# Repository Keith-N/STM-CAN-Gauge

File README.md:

# STM-CAN-Gauge

An STM32F042 based CAN gauge for use with rusEFI ECUs. <br/>
CAN is configured for 500k with a base ID of 512. <br/>
Input voltage tested at 5V and 12V. <br/>

Flash 'CAN Gauge.bin' through STM32CubeProgrammer using STLink and TC2030. <br/>

The only required connections for operation are supply voltage/ground and CAN High/Low. <br/>

Pinout from the back of connector.

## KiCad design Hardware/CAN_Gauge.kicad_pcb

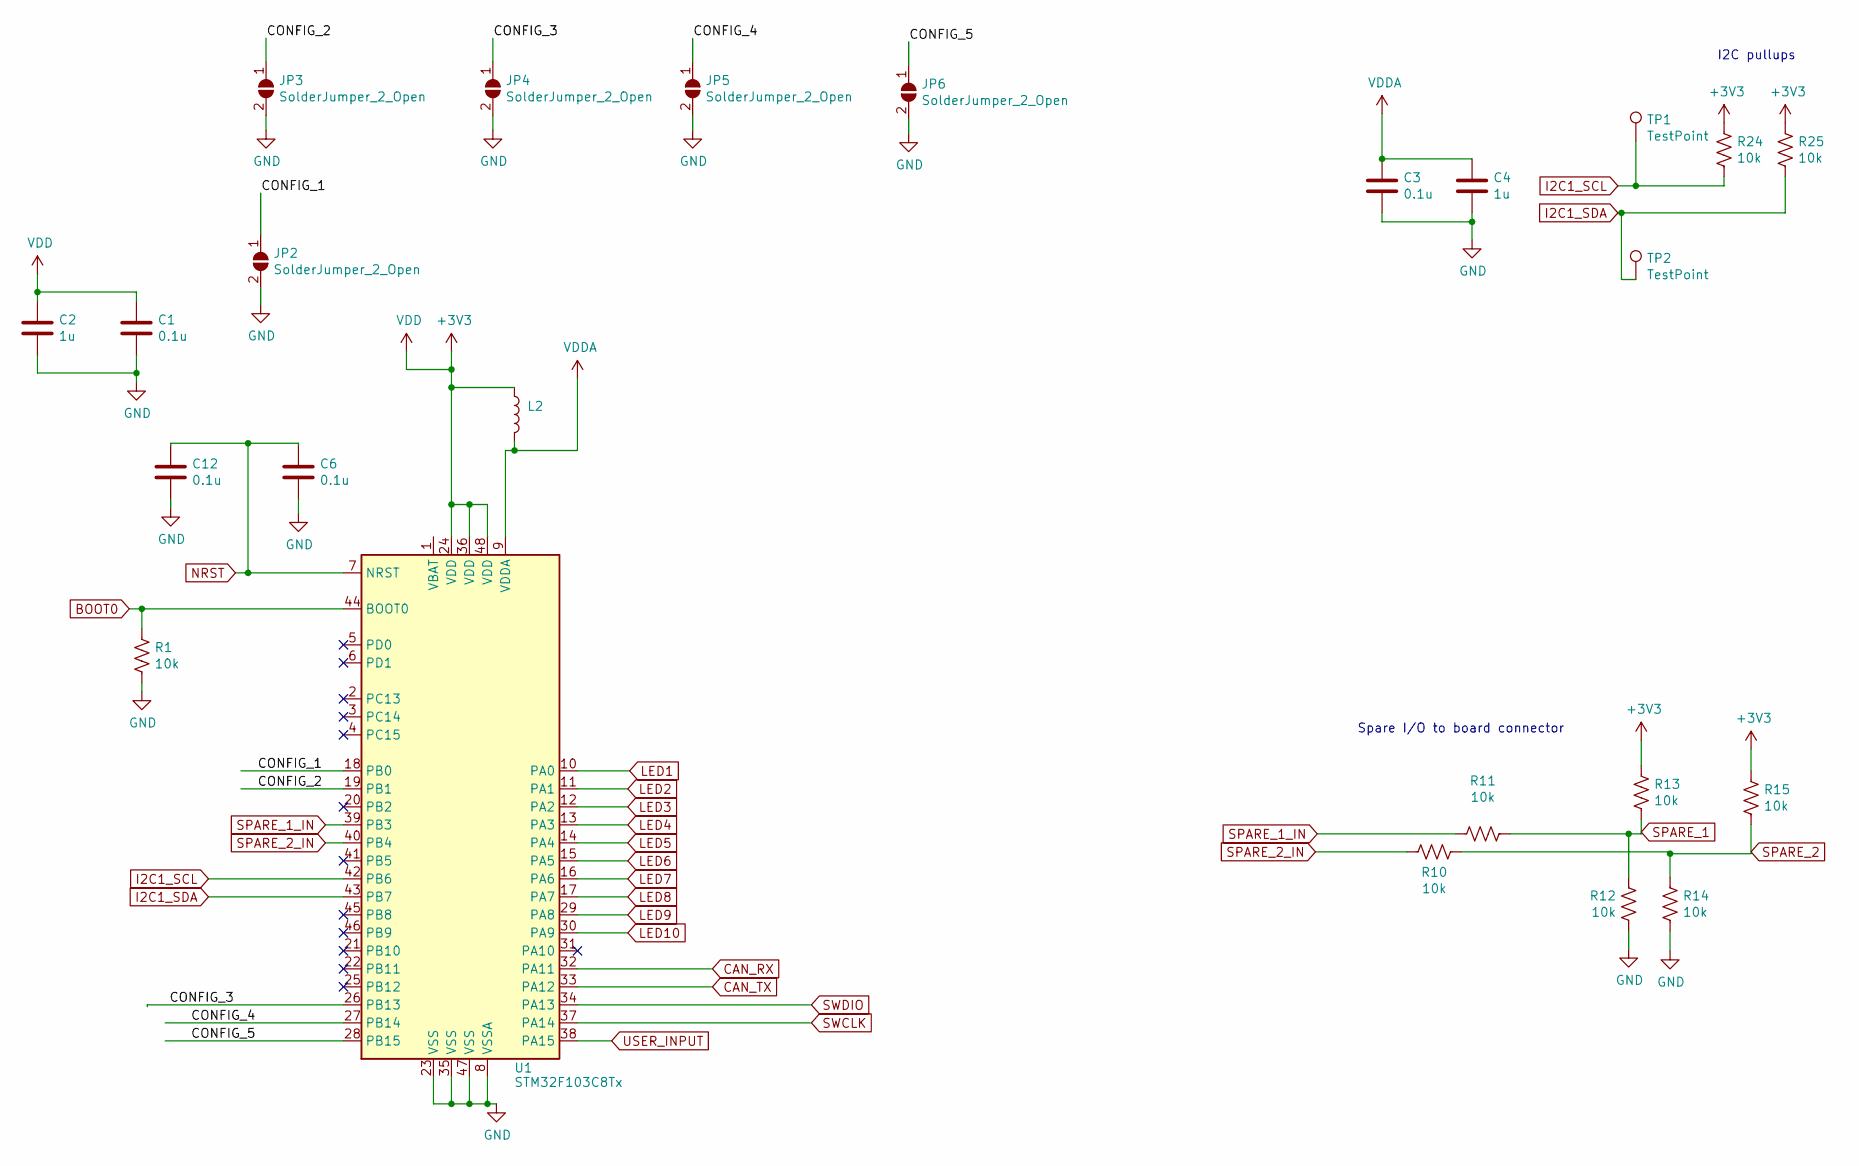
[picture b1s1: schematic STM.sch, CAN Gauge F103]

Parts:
C1, C3, C6, C12: 0.1u; C_0402_1005Metric; LCSC C2655418
C2, C4: 1u; C_0402_1005Metric; LCSC C389008
JP2, JP3, JP4, JP5, JP6: SolderJumper_2_Open; SolderJumper-2_P1.3mm_Open_Pad1.0x1.5mm
L2: 30; L_0402_1005Metric; LCSC C76886
R1, R10, R11, R12, R13, R14, R15, R24, R25: 10k; R_0402_1005Metric
TP1, TP2: TestPoint; TestPoint_Pad_D1.0mm
U1: STM32F103C8Tx; LQFP-48_7x7mm_P0.5mm; LCSC C8734

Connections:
/STM/CONFIG_1: JP2.1 (A), U1.18 (PB0)
/STM/CONFIG_2: JP3.1 (A), U1.19 (PB1)
/STM/CONFIG_3: JP4.1 (A), U1.26 (PB13)
/STM/CONFIG_4: JP5.1 (A), U1.27 (PB14)
/STM/CONFIG_5: JP6.1 (A), U1.28 (PB15)
BOOT0: R1.1, U1.44 (BOOT0)
CAN_RX: U1.32 (PA11); also elsewhere on the board
CAN_TX: U1.33 (PA12); also elsewhere on the board
GND: C1.2, C2.2, C3.2, C4.2, C6.2, C12.2, JP2.2 (B), JP3.2 (B), JP4.2 (B), JP5.2 (B), JP6.2 (B), R1.2, R12.1, R14.1, U1.8 (VSSA), U1.23 (VSS), U1.35 (VSS), U1.47 (VSS); also elsewhere on the board
I2C1_SCL: R24.1, TP1.1, U1.42 (PB6); also elsewhere on the board
I2C1_SDA: R25.1, TP2.1, U1.43 (PB7); also elsewhere on the board
LED1: U1.10 (PA0); also elsewhere on the board
LED2: U1.11 (PA1); also elsewhere on the board
LED3: U1.12 (PA2); also elsewhere on the board
LED4: U1.13 (PA3); also elsewhere on the board
LED5: U1.14 (PA4); also elsewhere on the board
LED6: U1.15 (PA5); also elsewhere on the board
LED7: U1.16 (PA6); also elsewhere on the board
LED8: U1.17 (PA7); also elsewhere on the board
LED9: U1.29 (PA8); also elsewhere on the board
LED10: U1.30 (PA9); also elsewhere on the board
NRST: C6.1, C12.1, U1.7 (NRST); also elsewhere on the board
OSC_IN: U1.3 (PC14)
OSC_OUT: U1.4 (PC15)
SPARE_1: R11.2, R12.2, R13.1; also elsewhere on the board
SPARE_1_IN: R11.1, U1.39 (PB3)
SPARE_2: R10.2, R14.2, R15.1; also elsewhere on the board
SPARE_2_IN: R10.1, U1.40 (PB4)
SWCLK: U1.37 (PA14); also elsewhere on the board
SWDIO: U1.34 (PA13); also elsewhere on the board
USER_INPUT: U1.38 (PA15); also elsewhere on the board
VDDA: C3.1, C4.1, L2.2, U1.9 (VDDA)

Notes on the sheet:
I2C pullups
Spare I/O to board connector

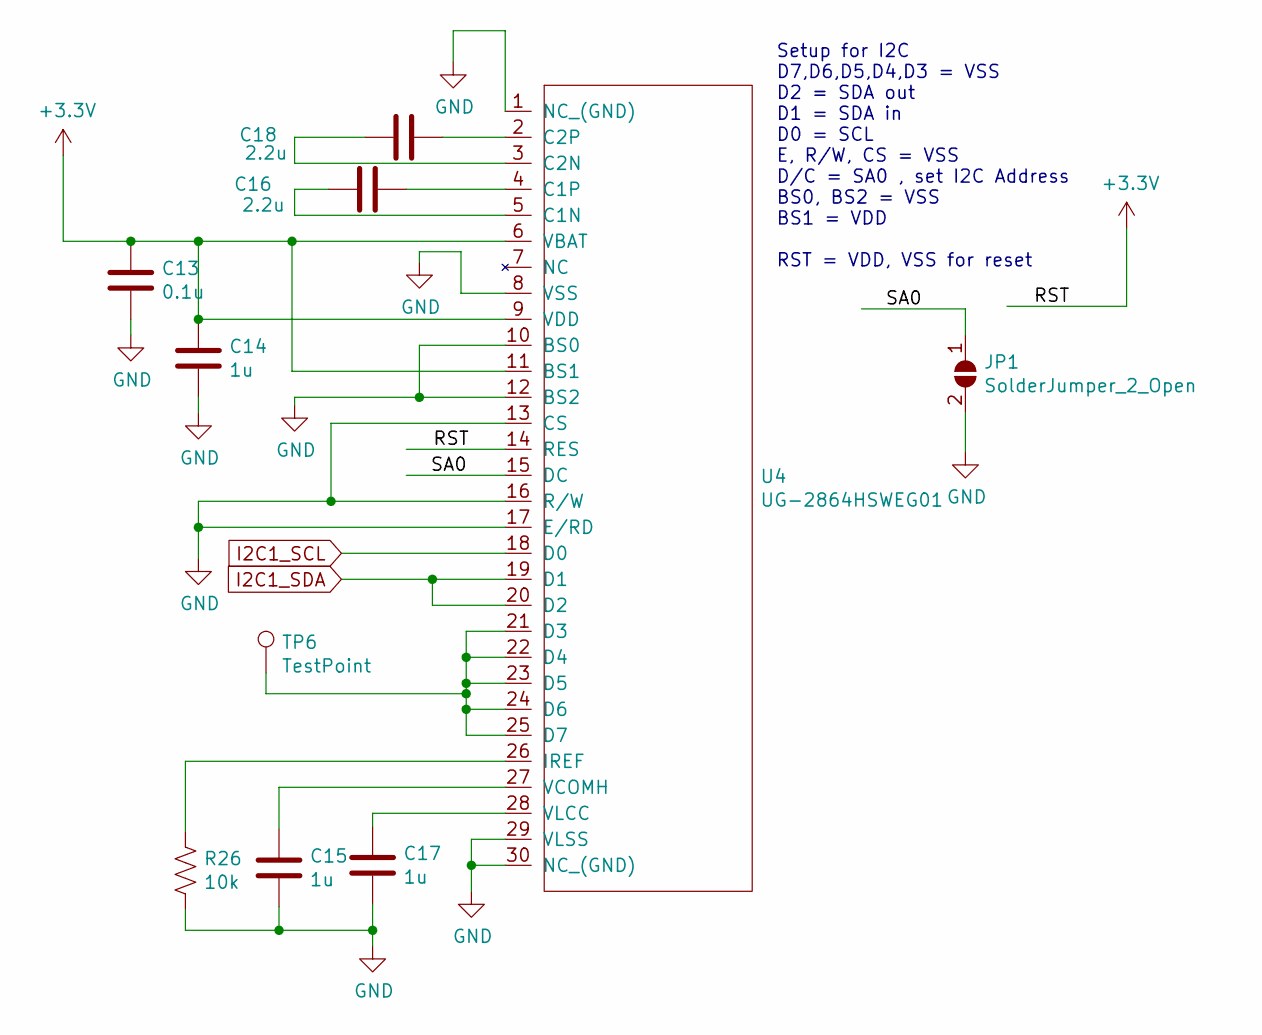
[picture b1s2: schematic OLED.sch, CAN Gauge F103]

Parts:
C13: 0.1u; C_0402_1005Metric; LCSC C1525
C14, C15, C17: 1u; C_0402_1005Metric; LCSC C52923
C16, C18: 2.2u; C_0402_1005Metric; LCSC C170151
JP1: SolderJumper_2_Open; SolderJumper-2_P1.3mm_Open_Pad1.0x1.5mm
R26: 10k; R_0402_1005Metric; LCSC C25744
TP6: TestPoint; TestPoint_Pad_D1.0mm
U4: UG-2864HSWEG01; SSH1106_Bottom; LCSC C2797216

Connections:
/OLED/SA0: JP1.1 (A), U4.15 (DC)
GND: C13.1, C14.1, C15.1, C17.1, JP1.2 (B), R26.1, U4.1 (NC_(GND)), U4.8 (VSS), U4.10 (BS0), U4.12 (BS2), U4.13 (CS), U4.16 (R/W), U4.17 (E/RD), U4.29 (VLSS), U4.30 (NC_(GND)); also elsewhere on the board
I2C1_SCL: U4.18 (D0); also elsewhere on the board
I2C1_SDA: U4.19 (D1), U4.20 (D2); also elsewhere on the board
unnamed: C15.2, U4.27 (VCOMH)
unnamed: C16.1, U4.5 (C1N)
unnamed: C16.2, U4.4 (C1P)
unnamed: C17.2, U4.28 (VLCC)
unnamed: C18.1, U4.3 (C2N)
unnamed: C18.2, U4.2 (C2P)
unnamed: R26.2, U4.26 (IREF)
unnamed: TP6.1, U4.21 (D3), U4.22 (D4), U4.23 (D5), U4.24 (D6), U4.25 (D7)

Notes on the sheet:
Setup for I2C D7,D6,D5,D4,D3 = VSS D2 = SDA out D1 = SDA in D0 = SCL E, R/W, CS = VSS D/C = SA0 , set I2C Address BS0, BS2 = VSS BS1 = VDD RST = VDD, VSS for reset

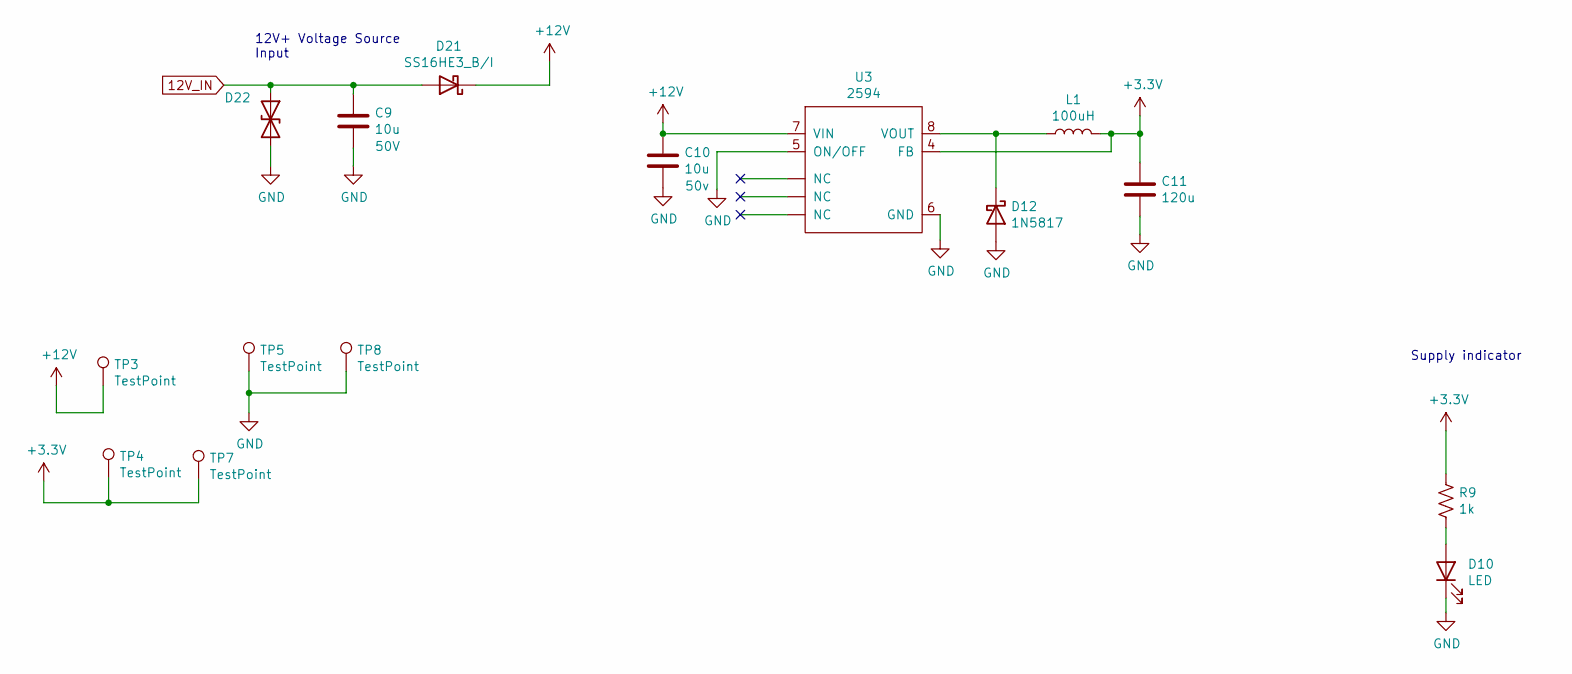
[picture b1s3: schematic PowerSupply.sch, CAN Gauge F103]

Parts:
C9: 10u; L_1206_3216Metric; Voltage 50V; Part Number CL31A106MBHNNNE; LCSC C13585
C10: 10u; L_1206_3216Metric; Voltage 50v
C11: 120u; C_1206_3216Metric; LCSC C15008
D10: LED; LED_0603_1608Metric; LCSC C2286
D12: 1N5817; D_SOD-123
D21: SS16HE3_B/I; D_SMA; Part Number SS16HE3_B/I; LCSC C211772
D22: SMBJ16CD-M3/H; D_SMB; Part Number SMBJ16CD-M3/H; LCSC C8830
L1: 100uH; L_0805_2012Metric; LCSC C68035
R9: 1k; R_0402_1005Metric; LCSC C11702
TP3, TP4, TP5, TP7, TP8: TestPoint; TestPoint_Pad_D1.0mm
U3: 2594; SOIC-8_3.9x4.9mm_P1.27mm; LCSC C316691

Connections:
12V_IN: C9.1, D21.2 (A), D22.1 (A1); also elsewhere on the board
+12V: C10.1, D21.1 (K), TP3.1, U3.7 (VIN)
GND: C9.2, C10.2, C11.2, D10.1 (K), D12.2 (A), D22.2 (A2), TP5.1, TP8.1, U3.5 (ON/OFF), U3.6 (GND); also elsewhere on the board
unnamed: D10.2 (A), R9.2
unnamed: D12.1 (K), L1.1, U3.8 (VOUT)

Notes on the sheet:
12V+ Voltage Source Input
Supply indicator

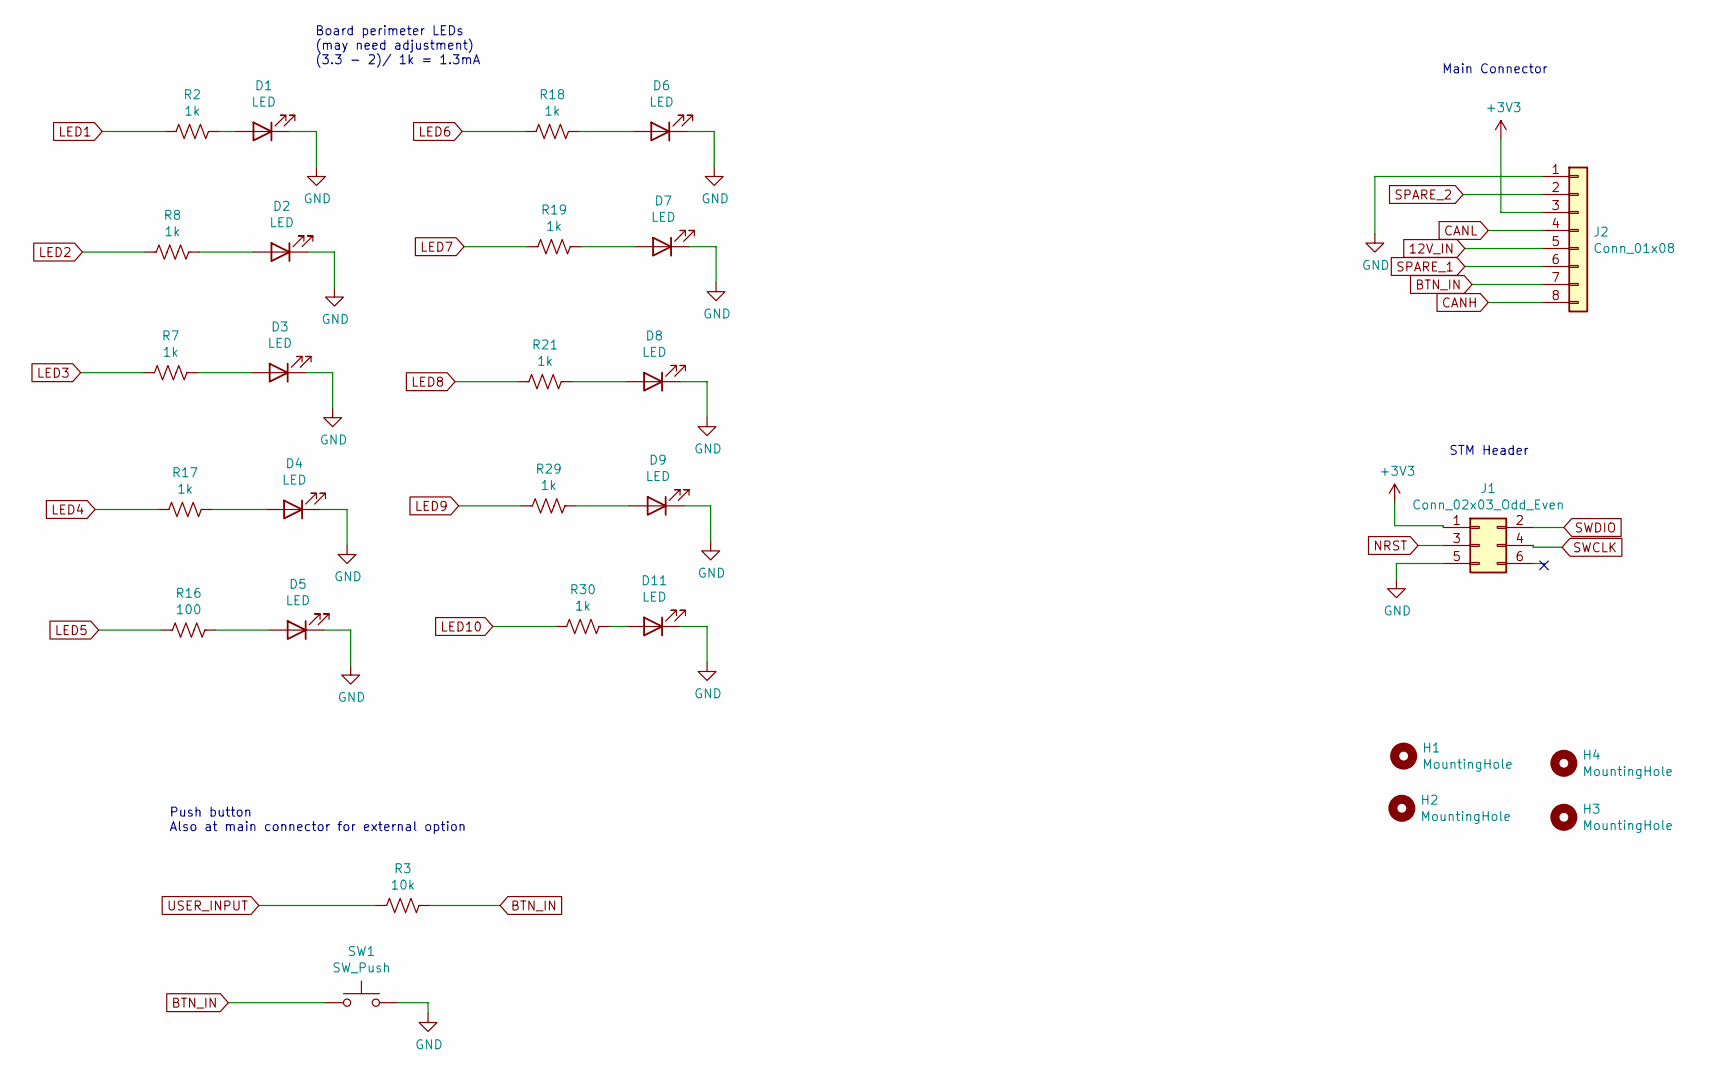
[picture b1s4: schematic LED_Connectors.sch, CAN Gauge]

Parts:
D1, D2, D3, D4, D5, D6, D7, D8, D9, D11: LED; LED_0603_1608Metric
H1, H2, H3, H4: MountingHole; MountingHole_2mm
J1: Conn_02x03_Odd_Even; Tag-Connect_TC2030-IDC-NL_2x03_P1.27mm_Vertical
J2: Conn_01x08; Molex_Micro-Fit_3.0_43045-0812_2x04_P3.00mm_Vertical
R2, R7, R8, R17, R18, R19, R21, R29, R30: 1k; R_0402_1005Metric
R3: 10k; R_0402_1005Metric; LCSC C60489
R16: 100; R_0402_1005Metric
SW1: SW_Push; SW_Push_1P1T_NO_6x6mm_H9.5mm; LCSC C480275

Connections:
12V_IN: J2.5; also elsewhere on the board
BTN_IN: J2.7, R3.1, SW1.1
CANH: J2.8; also elsewhere on the board
CANL: J2.4; also elsewhere on the board
GND: D1.1 (K), D2.1 (K), D3.1 (K), D4.1 (K), D5.1 (K), D6.1 (K), D7.1 (K), D8.1 (K), D9.1 (K), D11.1 (K), J1.5, J2.1, SW1.2; also elsewhere on the board
LED1: R2.2; also elsewhere on the board
LED2: R8.2; also elsewhere on the board
LED3: R7.2; also elsewhere on the board
LED4: R17.2; also elsewhere on the board
LED5: R16.2; also elsewhere on the board
LED6: R18.2; also elsewhere on the board
LED7: R19.2; also elsewhere on the board
LED8: R21.2; also elsewhere on the board
LED9: R29.2; also elsewhere on the board
LED10: R30.2; also elsewhere on the board
NRST: J1.3; also elsewhere on the board
unnamed: D1.2 (A), R2.1
unnamed: D2.2 (A), R8.1
unnamed: D3.2 (A), R7.1
unnamed: D4.2 (A), R17.1
unnamed: D5.2 (A), R16.1
unnamed: D6.2 (A), R18.1
unnamed: D7.2 (A), R19.1
unnamed: D8.2 (A), R21.1
unnamed: D9.2 (A), R29.1
unnamed: D11.2 (A), R30.1
SPARE_1: J2.6; also elsewhere on the board
SPARE_2: J2.2; also elsewhere on the board
SWCLK: J1.4; also elsewhere on the board
SWDIO: J1.2; also elsewhere on the board
USER_INPUT: R3.2; also elsewhere on the board

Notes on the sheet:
Board perimeter LEDs (may need adjustment) (3.3 - 2)/ 1k = 1.3mA
STM Header
Main Connector
Push button Also at main connector for external option

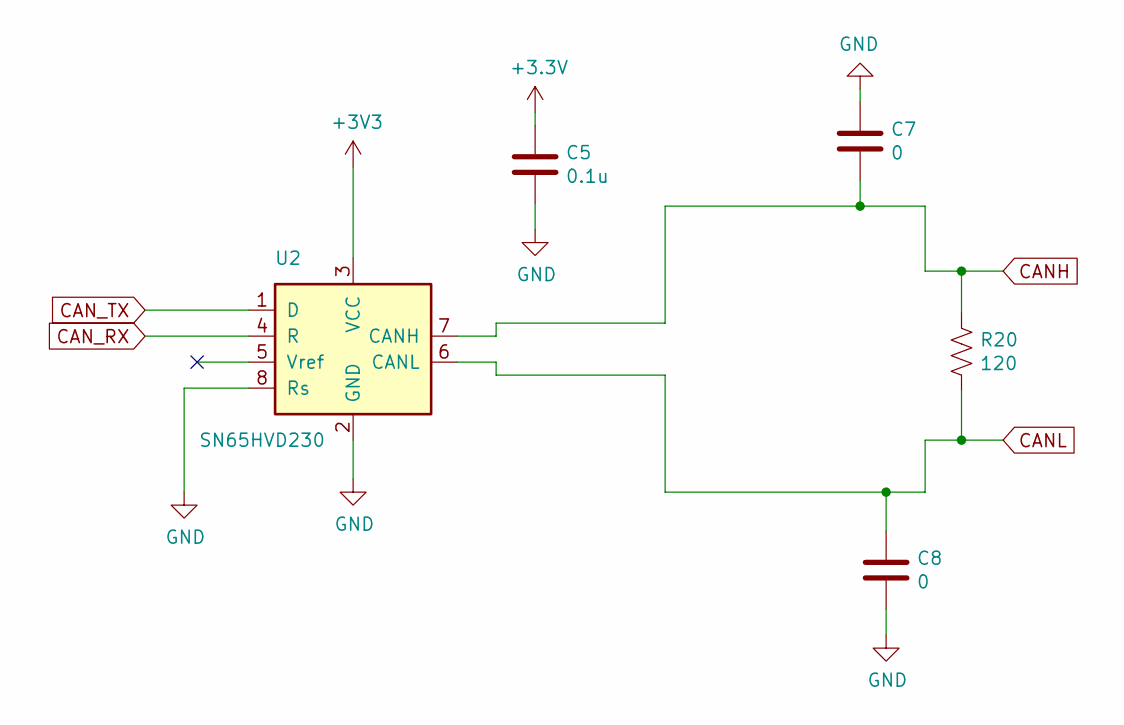
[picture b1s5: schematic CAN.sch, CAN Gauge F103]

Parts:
C5: 0.1u; C_0402_1005Metric
C7, C8: 0; C_0402_1005Metric
R20: 120; R_0402_1005Metric; LCSC C60310
U2: SN65HVD230; SOIC-8_3.9x4.9mm_P1.27mm; LCSC C12084

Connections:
CANH: C7.2, R20.1, U2.7 (CANH); also elsewhere on the board
CANL: C8.1, R20.2, U2.6 (CANL); also elsewhere on the board
CAN_RX: U2.4 (R); also elsewhere on the board
CAN_TX: U2.1 (D); also elsewhere on the board
GND: C5.2, C7.1, C8.2, U2.2 (GND), U2.8 (Rs); also elsewhere on the board

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
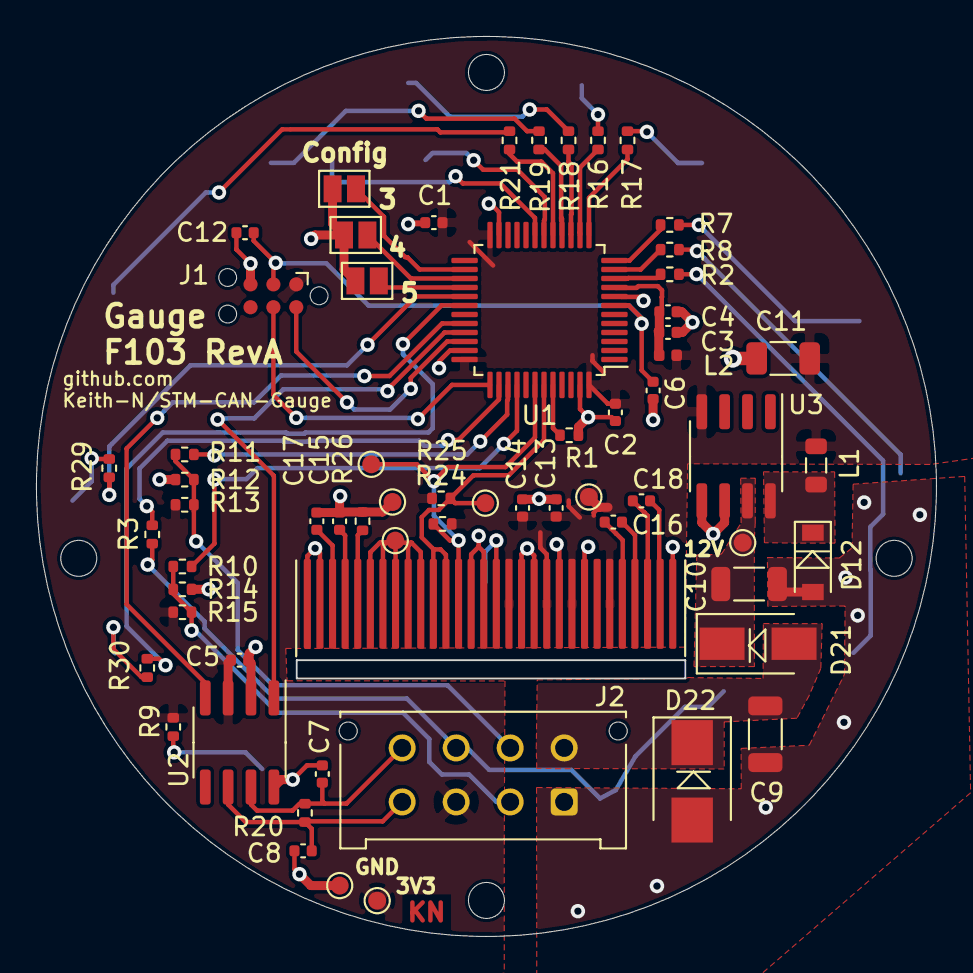
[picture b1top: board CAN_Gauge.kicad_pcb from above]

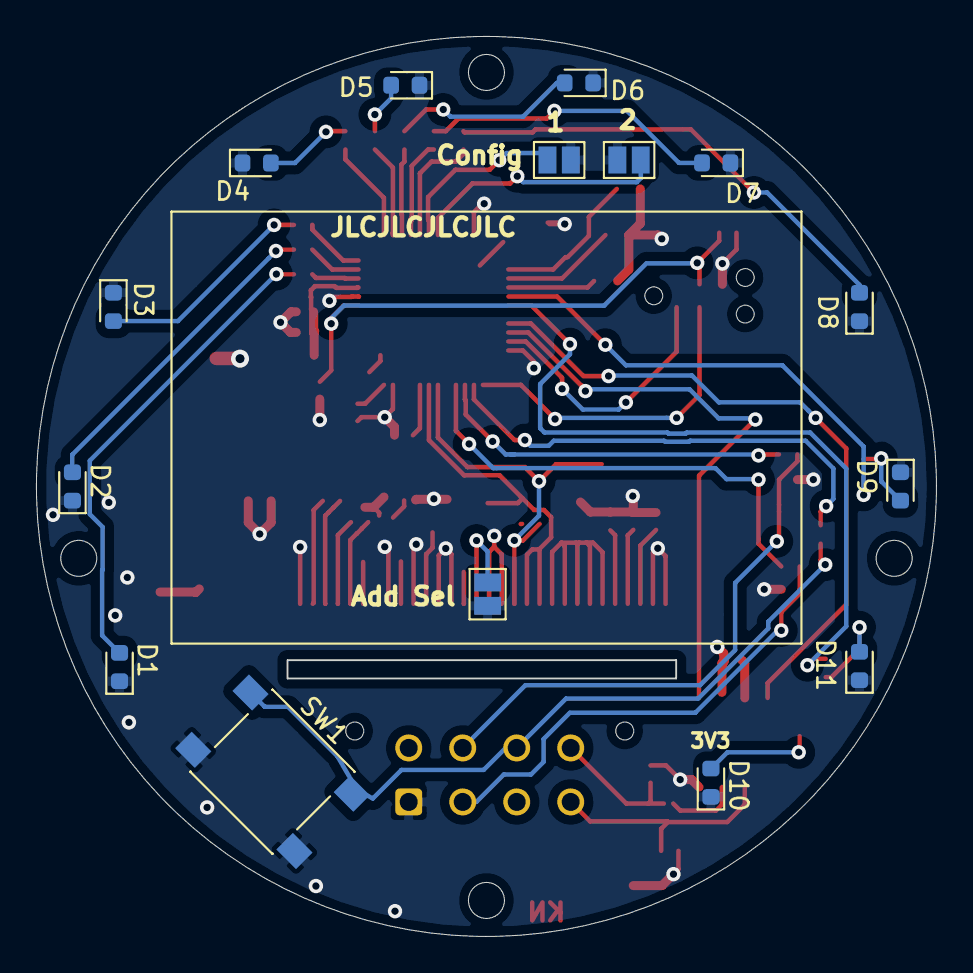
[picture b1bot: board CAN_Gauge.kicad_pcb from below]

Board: 2 copper layers, 50.0 x 49.9 mm, 82 parts (15 on the bottom side), 57 nets.

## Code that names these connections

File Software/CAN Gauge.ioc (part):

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Mcu.Name=STM32F042K(4-6)Tx
Mcu.Package=LQFP32
Mcu.UserName=STM32F042K6Tx
PA0.GPIOParameters=GPIO_PuPd,GPIO_Label
PA0.GPIO_Label=LED1
PA0.GPIO_PuPd=GPIO_PULLUP
PA0.Signal=GPIO_Output
PA1.GPIOParameters=GPIO_PuPd,GPIO_Label
PA1.GPIO_Label=LED2
PA1.GPIO_PuPd=GPIO_PULLUP
PA1.Signal=GPIO_Output
PA10.Mode=I2C
PA10.Signal=I2C1_SDA
PA11.Mode=CAN_Activate
PA11.Signal=CAN_RX
PA12.Mode=CAN_Activate
PA12.Signal=CAN_TX
PA13.GPIOParameters=GPIO_Label
PA13.GPIO_Label=SWDIO
PA13.Mode=Serial_Wire
PA13.Signal=SYS_SWDIO
PA14.GPIOParameters=GPIO_Label
PA14.GPIO_Label=SWCLK
PA14.Mode=Serial_Wire
PA14.Signal=SYS_SWCLK
PA15.GPIOParameters=GPIO_Label
PA15.GPIO_Label=LED10
PA15.Signal=GPIO_Output
PA2.GPIOParameters=GPIO_PuPd,GPIO_Label
PA2.GPIO_Label=LED3
PA2.GPIO_PuPd=GPIO_PULLUP
PA2.Signal=GPIO_Output
PA3.GPIOParameters=GPIO_PuPd,GPIO_Label
PA3.GPIO_Label=LED4
PA3.GPIO_PuPd=GPIO_PULLUP
PA3.Signal=GPIO_Output
PA4.GPIOParameters=GPIO_PuPd,GPIO_Label
PA4.GPIO_Label=LED5
PA4.GPIO_PuPd=GPIO_PULLUP
PA4.Signal=GPIO_Output
PA5.GPIOParameters=GPIO_PuPd,GPIO_Label
PA5.GPIO_Label=LED6
PA5.GPIO_PuPd=GPIO_PULLUP
PA5.Signal=GPIO_Output
PA6.GPIOParameters=GPIO_PuPd,GPIO_Label
PA6.GPIO_Label=LED7
PA6.GPIO_PuPd=GPIO_PULLUP
PA6.Signal=GPIO_Output
PA7.GPIOParameters=GPIO_PuPd,GPIO_Label
PA7.GPIO_Label=LED8
PA7.GPIO_PuPd=GPIO_PULLUP
PA7.Signal=GPIO_Output
PA8.GPIOParameters=GPIO_PuPd,GPIO_Label
PA8.GPIO_Label=LED9
PA8.GPIO_PuPd=GPIO_PULLUP
PA8.Signal=GPIO_Output
PA9.Mode=I2C
PA9.Signal=I2C1_SCL
PB0.GPIOParameters=GPIO_PuPd,GPIO_Label
PB0.GPIO_Label=config1
PB0.GPIO_PuPd=GPIO_PULLUP
PB0.Signal=GPIO_Input
PB1.GPIOParameters=GPIO_PuPd,GPIO_Label
PB1.GPIO_Label=config2
PB1.GPIO_PuPd=GPIO_PULLUP
PB1.Signal=GPIO_Input
PB4.GPIOParameters=GPIO_PuPd,GPIO_Label,GPIO_ModeDefaultEXTI
PB4.GPIO_Label=button
PB4.GPIO_ModeDefaultEXTI=GPIO_MODE_IT_FALLING
PB4.GPIO_PuPd=GPIO_PULLUP
PB4.Signal=GPXTI4
PB5.GPIOParameters=GPIO_Label
PB5.GPIO_Label=SPARE_1
PB5.Signal=GPIO_Input
PB6.GPIOParameters=GPIO_Label
PB6.GPIO_Label=SPARE_2
PB6.Signal=GPIO_Input
PF0-OSC_IN.GPIOParameters=GPIO_Label
PF0-OSC_IN.GPIO_Label=MCO
PF0-OSC_IN.Mode=HSE-External-Clock-Source
PF0-OSC_IN.Signal=RCC_OSC_IN
board=NUCLEO-F042K6
boardIOC=true

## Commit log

2021-08-29 Initial Commit
    Upload Files
2021-08-29 Update file locations
2021-08-29 Add Readme
2021-09-27 Update functions, add display rotation
    Added text size to function input to clean up some redundant functions, added 90 rotated display
2021-10-11 Restructure and add PCB
    Add Schematic, PCB, restructure directories
2021-10-11 Cleanup
2021-10-11 Add PDFs
    Add PDFs of schematic and PCB
2021-10-15 Add config resistors
    Add resistors for adjusting configuration settings
2021-10-30 Rev B
    Update STM package, switcher circuit, layout
2021-10-31 Update components for assembly, generate gerbers
2021-12-11 Update board layout
    Fix OLED pads to meet intended design. Move all non UI components to one side of the board for better single sided assembly.
2021-12-28 Add LED ring functionality
    Control the outer LEDs based on the range of the current data. Also add code for Teensy 3.6 used to send test data over CAN.
2022-01-15 Add functions to code
    Add config settings, different gauges, unit conversions
2022-01-19 Scaling updates
    Some issues with MAP scaling were adjusted.
2022-01-22 Update MAP scaling
2022-01-25 Update for F103
2022-01-25 Work in progress
2022-01-27 OLED Initialization
    Initialize OLED more than once, seems to help with loss of OLED during rapid power cycle. Work in progress...
2022-01-29 Update pcb
2022-01-30 Generate files
2022-01-30 Adjust scaling and offset
    Use multiplier values to do all scaling. Account for added offsets
2022-02-05 Update scaling and variables
    Update scaling, rename variables to make their purpose more clear, adjust LED startup sequence, adjust MAF scaling
2022-02-05 OLED init updates
    Add delay to startup and initialization for OLED
2022-02-05 OLED Initialization Updates
2022-02-09 Clean up files
2022-02-14 Update scaling, decimal printing, and cleanup
    Adjust scaling calculations to use floats. Decimal printing is configured per data and either always or never shows, two places. Cleaned up some unused code.
2022-02-15 PCB updates, Generate Gerbers, BOM, and position files
2022-04-09 Add speed to gauges
    Add gauges for speed in MPH and KPH
2022-04-10 Update speed calc
    Update MPH calculation
